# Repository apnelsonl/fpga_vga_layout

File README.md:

Files for PCB layout using KiCAD

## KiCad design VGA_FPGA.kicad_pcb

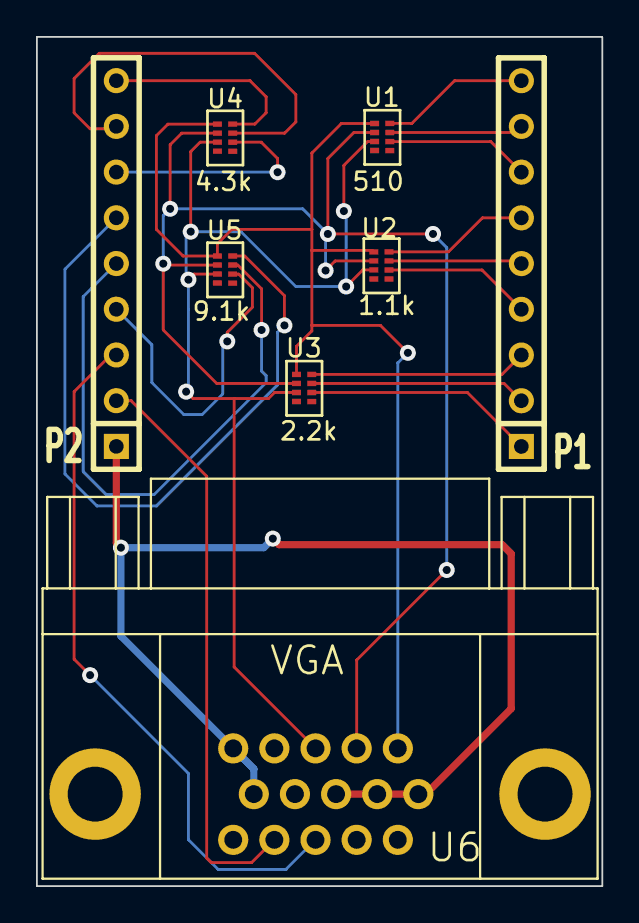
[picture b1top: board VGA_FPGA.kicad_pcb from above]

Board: 2 copper layers, 31.4 x 47.2 mm, 8 parts (0 on the bottom side), 21 nets.

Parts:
P1, P2: SIL-9
U1: 510; R_ARR
U2: 1.1k; R_ARR
U3: 2.2k; R_ARR
U4: 4.3k; R_ARR
U5: 9.1k; R_ARR
U6: VGA; VGA_Female

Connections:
/HSYNC: P2.3, U6.13
/VSYNC: P2.2, U6.14
GND: P2.1, U6.5, U6.6, U6.7, U6.8, U6.10
unnamed: P1.2, U3.2
unnamed: P1.6, U2.1
unnamed: P1.5, U2.2
unnamed: P1.4, U2.3
unnamed: P1.3, U3.1
unnamed: P1.1, U3.3
unnamed: P2.9, U4.1
unnamed: P2.8, U4.2
unnamed: U1.7, U2.7, U3.7, U4.7, U5.7, U6.3
unnamed: P1.9, U1.1
unnamed: P1.8, U1.2
unnamed: P1.7, U1.3
unnamed: P2.4, U5.3
unnamed: P2.7, U4.3
unnamed: P2.6, U5.1
unnamed: P2.5, U5.2
unnamed: U1.6, U2.6, U3.6, U4.6, U5.6, U6.2
unnamed: U1.5, U2.5, U3.5, U4.5, U5.5, U6.1

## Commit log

2013-11-19 add layout and gerber files
